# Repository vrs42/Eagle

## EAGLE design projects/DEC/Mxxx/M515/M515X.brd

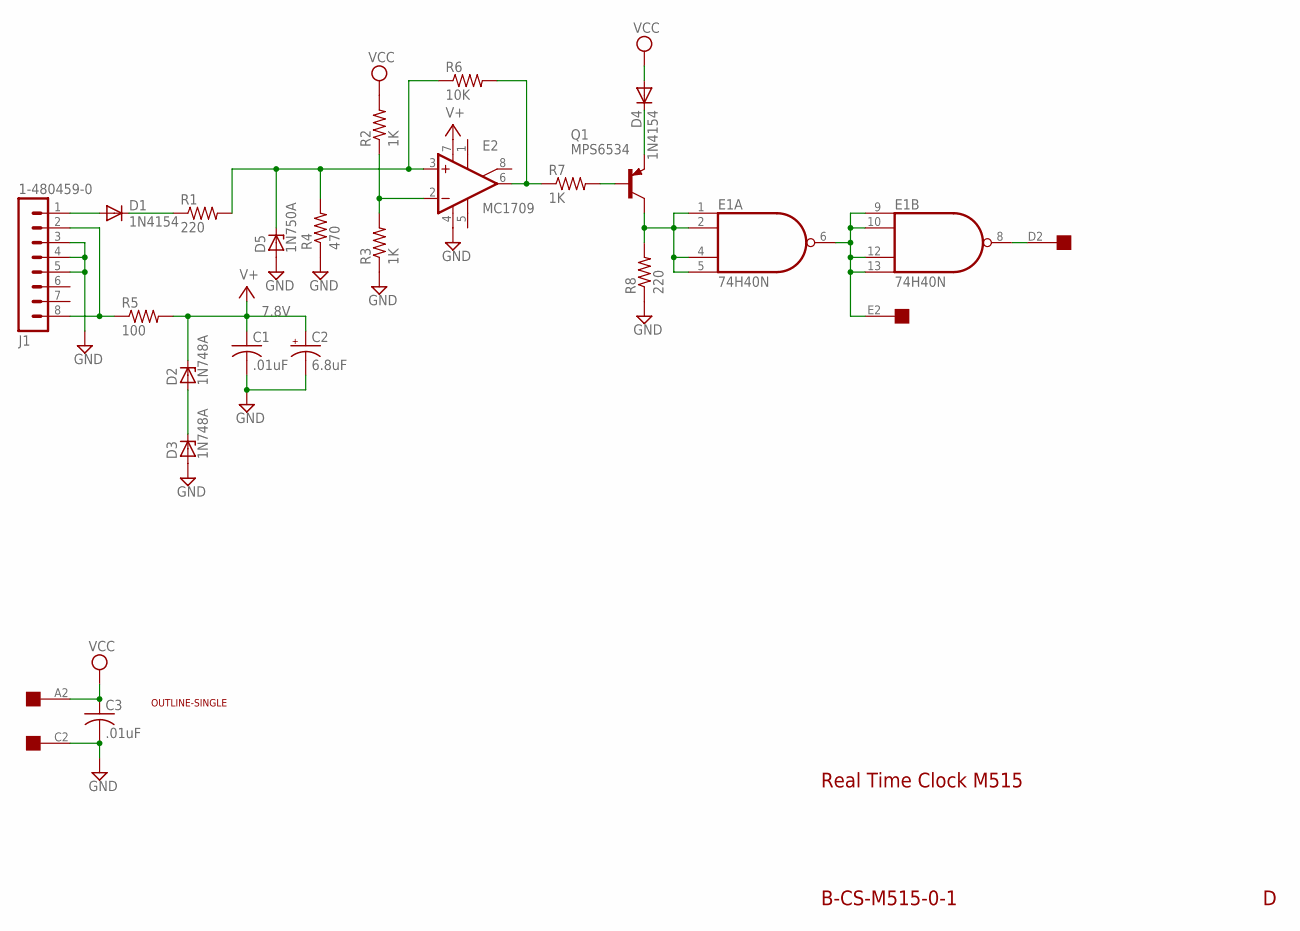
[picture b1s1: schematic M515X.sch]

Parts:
C1, C3: .01uF; C050-025X075
C2: 6.8uF; E12-8
D1, D4: 1N4154; DO35-10
D2, D3: 1N748A; DO35Z10
D5: 1N750A; DO35Z10
E1: 74H40N; DIL14
E2: MC1709; H08C
J1: 1-480459-0
Q1: MPS6534; TO5
R1, R8: 220; 0207/10
R2, R3, R7: 1K; 0207/10
R4: 470; 0207/10
R5: 100; 0207/10
R6: 10K; 0207/10
U$1: OUTLINE-SINGLE; SINGLE
U$3: EDGE-1; EDGE-CON1

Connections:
GND: C1.2, C2.-, C3.2, D3.A, D5.A, E1.7 (GND), E2.4 (V-), J1.3, J1.4, J1.5, R3.1, R4.1, R8.1, U$3.C2
unnamed: D1.A, J1.1
unnamed: D2.A, D3.C
unnamed: J1.2, J1.8, R5.1
unnamed: D1.C, R1.1
unnamed: D5.C, E2.3 (+IN), R1.2, R4.2, R6.1
unnamed: E1.8 (O), U$3.D2
unnamed: E1.6 (O), E1.9 (I0), E1.10 (I1), E1.12 (I2), E1.13 (I3), U$3.E2
unnamed: E1.1 (I0), E1.2 (I1), E1.4 (I2), E1.5 (I3), Q1.3 (C), R8.2
unnamed: D4.C, Q1.1 (E)
unnamed: Q1.2 (B), R7.2
unnamed: E2.6 (OUT), R6.2, R7.1
unnamed: E2.2 (-IN), R2.1, R3.2
V+: C1.1, C2.+, D2.C, E2.7 (V+), R5.2
VCC: C3.1, D4.A, E1.14 (VCC), R2.2, U$3.A2

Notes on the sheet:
7.8V
B-CS-M515-0-1
Real Time Clock M515

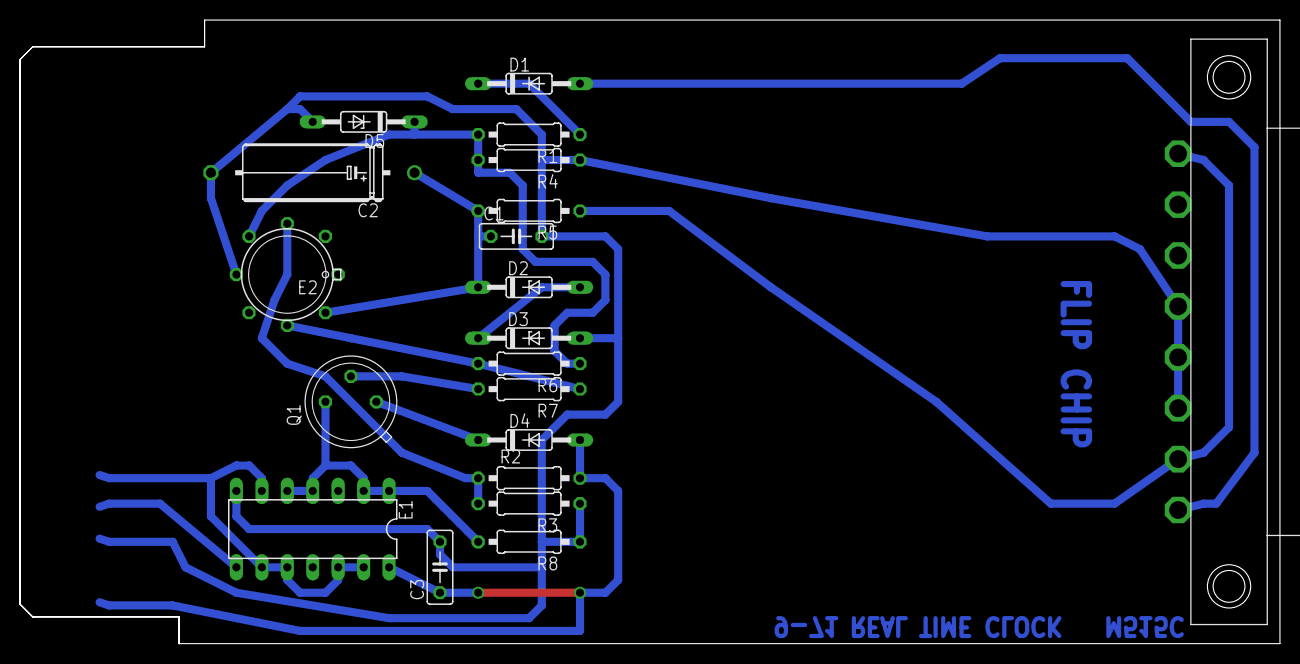
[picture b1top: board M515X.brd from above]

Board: 2 copper layers, 125.7 x 62.2 mm, 22 parts (0 on the bottom side), 15 nets.

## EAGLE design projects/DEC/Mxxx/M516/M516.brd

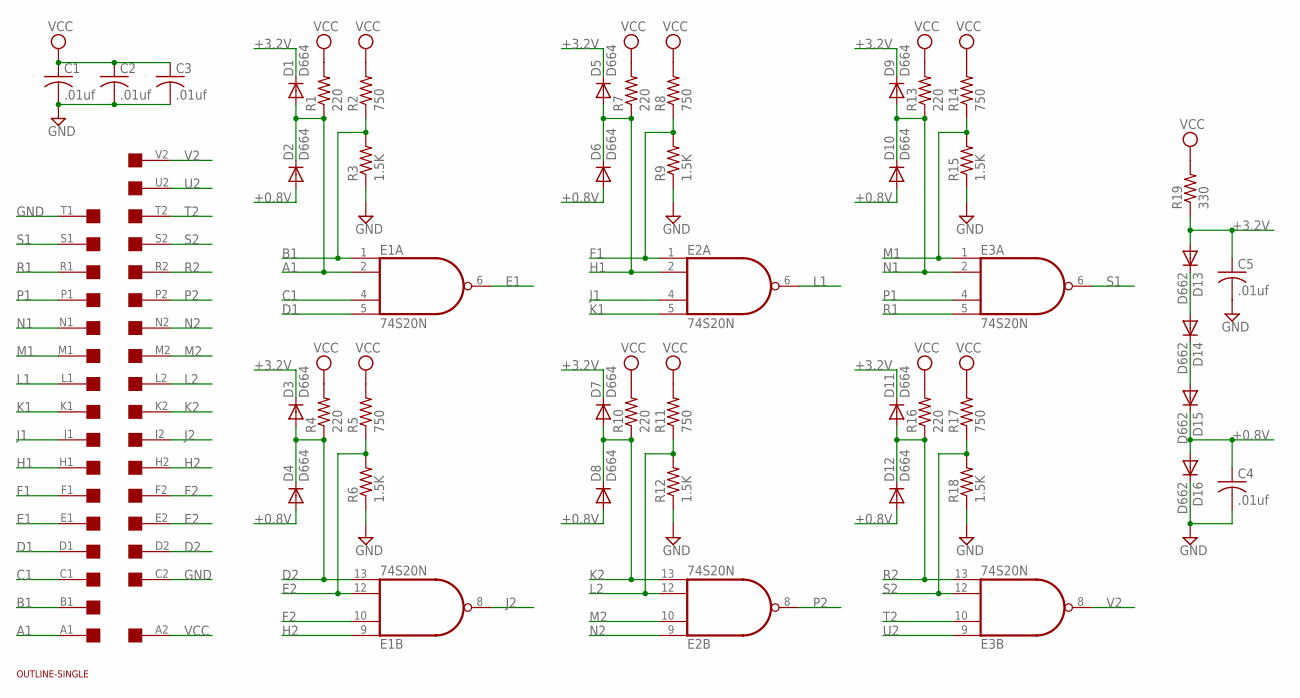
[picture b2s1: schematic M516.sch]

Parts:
C1, C2, C3, C4, C5: .01uf; C050-025X075
D1, D2, D3, D4, D5, D6, D7, D8, D9, D10, D11, D12: D664; DO35-10
D13, D14, D15, D16: D662; DO35-10
E1, E2, E3: 74S20N; DIL14
R1, R4, R7, R10, R13, R16: 220; 0207/10
R2, R5, R8, R11, R14, R17: 750; 0207/10
R3, R6, R9, R12, R15, R18: 1.5K; 0207/10
R19: 330; 0207/10
U$1: OUTLINE-SINGLE; SINGLE
U$2: SINGLE; EDGE-CON2

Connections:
+0.8V: C4.1, D2.A, D4.A, D6.A, D8.A, D10.A, D12.A, D15.C, D16.A
+3.2V: C5.1, D1.C, D3.C, D5.C, D7.C, D9.C, D11.C, D13.A, R19.1
A1: D1.A, D2.C, E1.2 (I1), R1.1, U$2.A1
B1: E1.1 (I0), R2.1, R3.2, U$2.B1
C1: E1.4 (I2), U$2.C1
D1: E1.5 (I3), U$2.D1
D2: D3.A, D4.C, E1.13 (I3), R4.1, U$2.D2
E1: E1.6 (O), U$2.E1
E2: E1.12 (I2), R5.1, R6.2, U$2.E2
F1: E2.1 (I0), R8.1, R9.2, U$2.F1
F2: E1.10 (I1), U$2.F2
GND: C1.2, C2.2, C3.2, C4.2, C5.2, D16.C, E1.7 (GND), E2.7 (GND), E3.7 (GND), R3.1, R6.1, R9.1, R12.1, R15.1, R18.1, U$2.C2, U$2.T1
H1: D5.A, D6.C, E2.2 (I1), R7.1, U$2.H1
H2: E1.9 (I0), U$2.H2
J1: E2.4 (I2), U$2.J1
J2: E1.8 (O), U$2.J2
K1: E2.5 (I3), U$2.K1
K2: D7.A, D8.C, E2.13 (I3), R10.1, U$2.K2
L1: E2.6 (O), U$2.L1
L2: E2.12 (I2), R11.1, R12.2, U$2.L2
M1: E3.1 (I0), R14.1, R15.2, U$2.M1
M2: E2.10 (I1), U$2.M2
N1: D9.A, D10.C, E3.2 (I1), R13.1, U$2.N1
N2: E2.9 (I0), U$2.N2
unnamed: D13.C, D14.A
unnamed: D14.C, D15.A
P1: E3.4 (I2), U$2.P1
P2: E2.8 (O), U$2.P2
R1: E3.5 (I3), U$2.R1
R2: D11.A, D12.C, E3.13 (I3), R16.1, U$2.R2
S1: E3.6 (O), U$2.S1
S2: E3.12 (I2), R17.1, R18.2, U$2.S2
T2: E3.10 (I1), U$2.T2
U2: E3.9 (I0), U$2.U2
V2: E3.8 (O), U$2.V2
VCC: C1.1, C2.1, C3.1, E1.14 (VCC), E2.14 (VCC), E3.14 (VCC), R1.2, R2.2, R4.2, R5.2, R7.2, R8.2, R10.2, R11.2, R13.2, R14.2, R16.2, R17.2, R19.2, U$2.A2

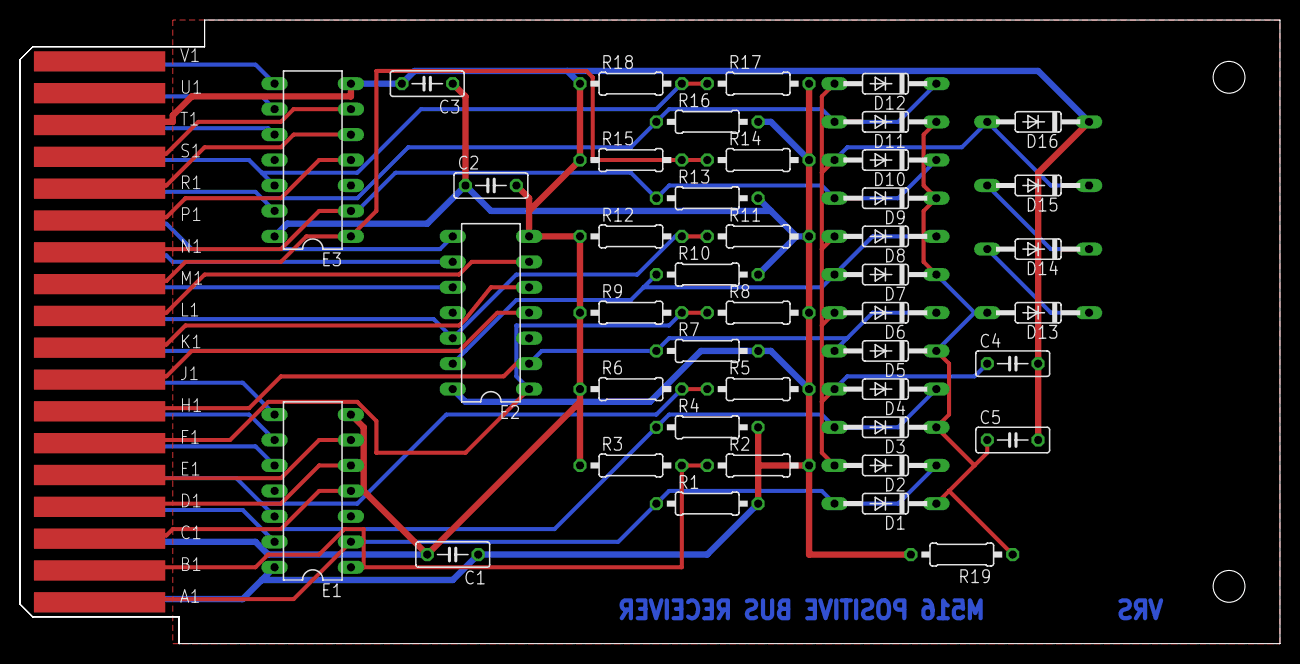
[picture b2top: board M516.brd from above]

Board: 2 copper layers, 125.7 x 62.2 mm, 45 parts (0 on the bottom side), 36 nets.

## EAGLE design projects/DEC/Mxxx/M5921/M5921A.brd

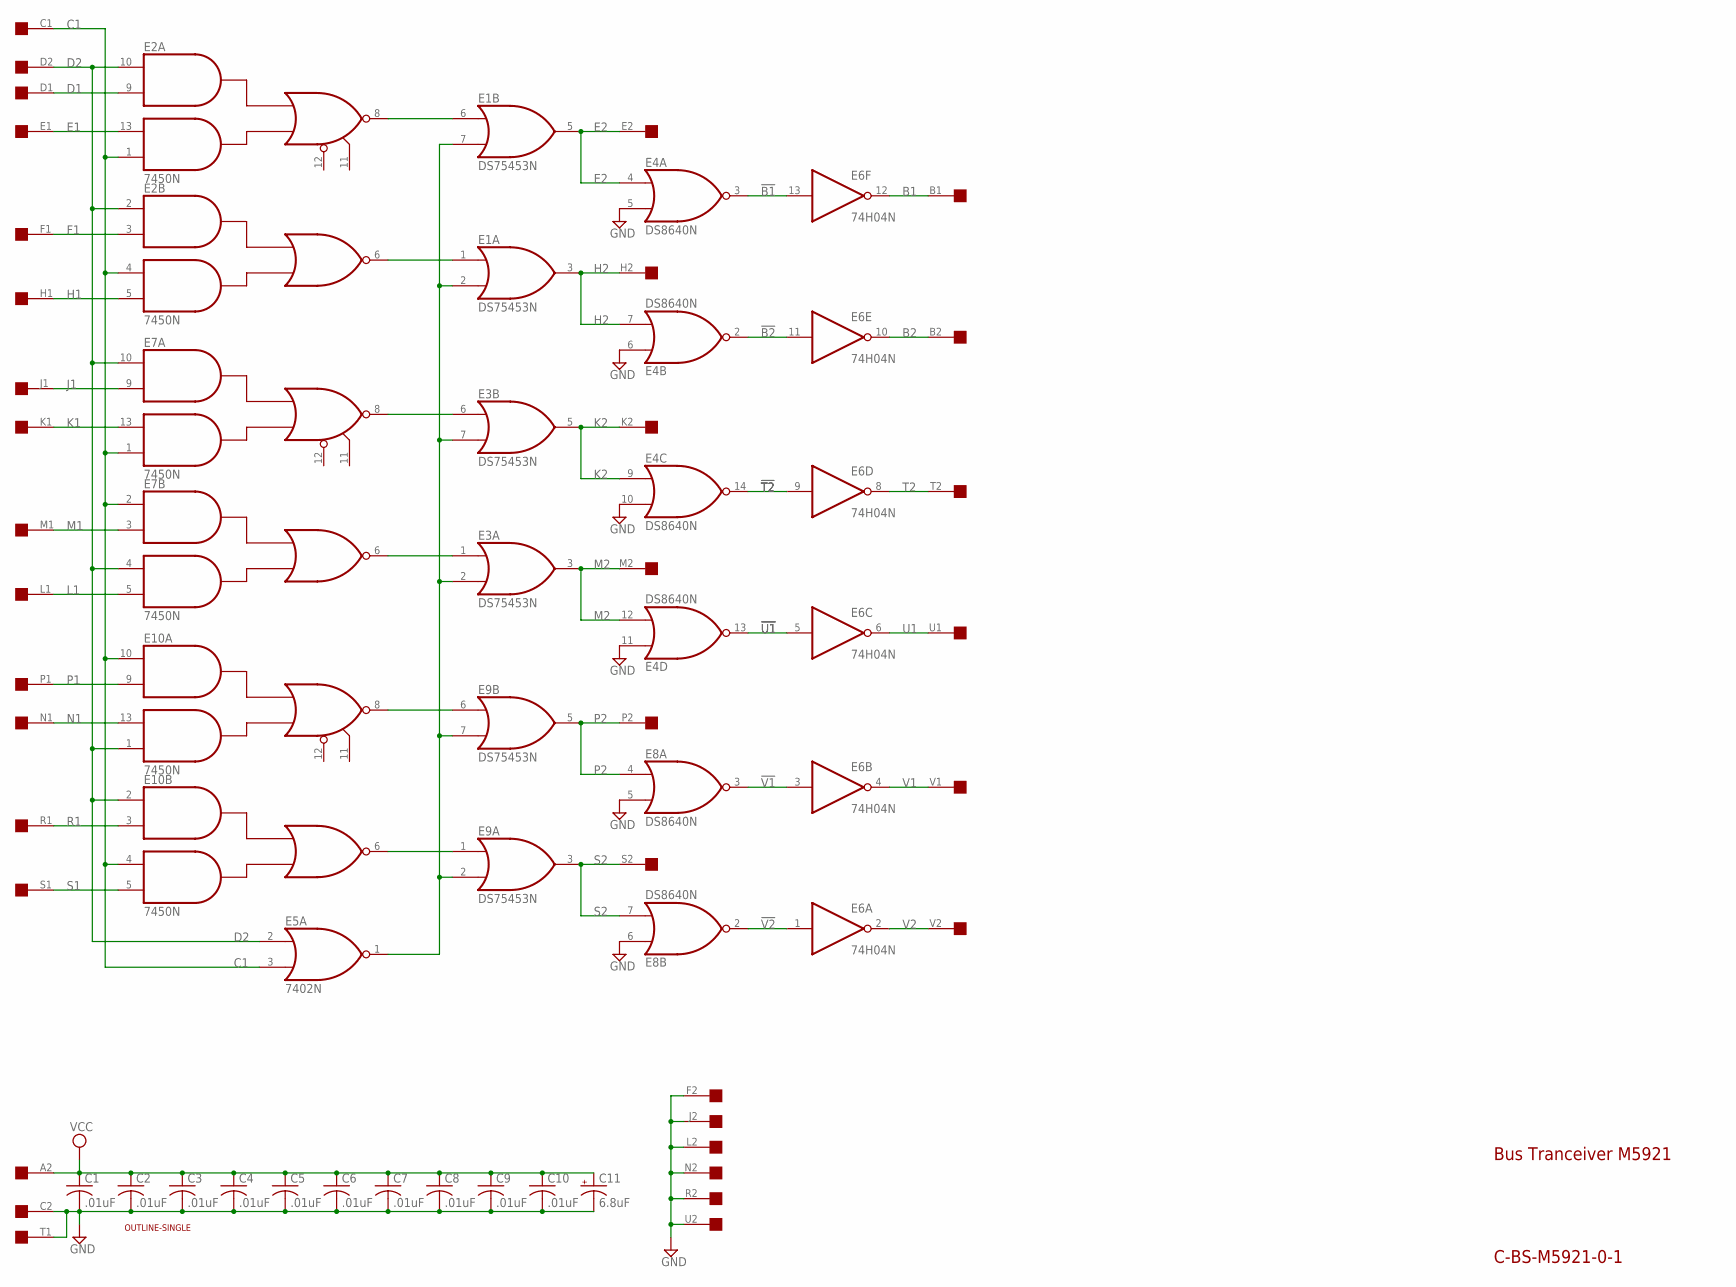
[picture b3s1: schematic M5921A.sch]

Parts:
C1, C2, C3, C4, C5, C6, C7, C8, C9, C10: .01uF; C063-025X075
C11: 6.8uF; E15-5
E1, E3, E9: DS75453N; DIL08
E2, E7, E10: 7450N; DIL14
E4, E8: DS8640N; DIL14
E5: 7402N; DIL14
E6: 74H04N; DIL14
U$1: OUTLINE-SINGLE; SINGLE
U$2: edge; EDGE-CON2

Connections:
!B1: E4.3 (O), E6.13 (I)
!B2: E4.2 (O), E6.11 (I)
!T2: E4.14 (O), E6.9 (I)
!U1: E4.13 (O), E6.5 (I)
!V1: E6.3 (I), E8.3 (O)
!V2: E6.1 (I), E8.2 (O)
B1: E6.12 (O), U$2.B1
B2: E6.10 (O), U$2.B2
C1: E2.1 (I4), E2.4 (I3), E5.3 (I1), E7.1 (I4), E7.2 (I1), E10.4 (I3), E10.10 (I1), U$2.C1
D1: E2.9 (I2), U$2.D1
D2: E2.2 (I1), E2.10 (I1), E5.2 (I0), E7.4 (I3), E7.10 (I1), E10.1 (I4), E10.2 (I1), U$2.D2
E1: E2.13 (I3), U$2.E1
E2: E1.5 (O), E4.4 (I0), U$2.E2
F1: E2.3 (I2), U$2.F1
GND: C1.2, C2.2, C3.2, C4.2, C5.2, C6.2, C7.2, C8.2, C9.2, C10.2, C11.-, E1.4 (GND), E2.7 (GND), E3.4 (GND), E4.1 (GND), E4.5 (I1), E4.6 (I0), E4.10 (I1), E4.11 (I0), E5.7 (GND), E6.7 (GND), E7.7 (GND), E8.1 (GND), E8.5 (I1), E8.6 (I0), E9.4 (GND), E10.7 (GND), U$2.C2, U$2.F2, U$2.J2, U$2.L2, U$2.N2, U$2.R2, U$2.T1, U$2.U2
H1: E2.5 (I4), U$2.H1
H2: E1.3 (O), E4.7 (I1), U$2.H2
J1: E7.9 (I2), U$2.J1
K1: E7.13 (I3), U$2.K1
K2: E3.5 (O), E4.9 (I0), U$2.K2
L1: E7.5 (I4), U$2.L1
M1: E7.3 (I2), U$2.M1
M2: E3.3 (O), E4.12 (I1), U$2.M2
N1: E10.13 (I3), U$2.N1
unnamed: E1.1 (I0), E2.6 (O)
unnamed: E1.6 (I0), E2.8 (O)
unnamed: E1.2 (I1), E1.7 (I1), E3.2 (I1), E3.7 (I1), E5.1 (O), E9.2 (I1), E9.7 (I1)
unnamed: E3.6 (I0), E7.8 (O)
unnamed: E3.1 (I0), E7.6 (O)
unnamed: E9.6 (I0), E10.8 (O)
unnamed: E9.1 (I0), E10.6 (O)
P1: E10.9 (I2), U$2.P1
P2: E8.4 (I0), E9.5 (O), U$2.P2
R1: E10.3 (I2), U$2.R1
S1: E10.5 (I4), U$2.S1
S2: E8.7 (I1), E9.3 (O), U$2.S2
T2: E6.8 (O), U$2.T2
U1: E6.6 (O), U$2.U1
V1: E6.4 (O), U$2.V1
V2: E6.2 (O), U$2.V2
VCC: C1.1, C2.1, C3.1, C4.1, C5.1, C6.1, C7.1, C8.1, C9.1, C10.1, C11.+, E1.8 (VCC), E2.14 (VCC), E3.8 (VCC), E4.8 (VCC), E5.14 (VCC), E6.14 (VCC), E7.14 (VCC), E8.8 (VCC), E9.8 (VCC), E10.14 (VCC), U$2.A2

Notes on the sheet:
Bus Tranceiver M5921
C-BS-M5921-0-1

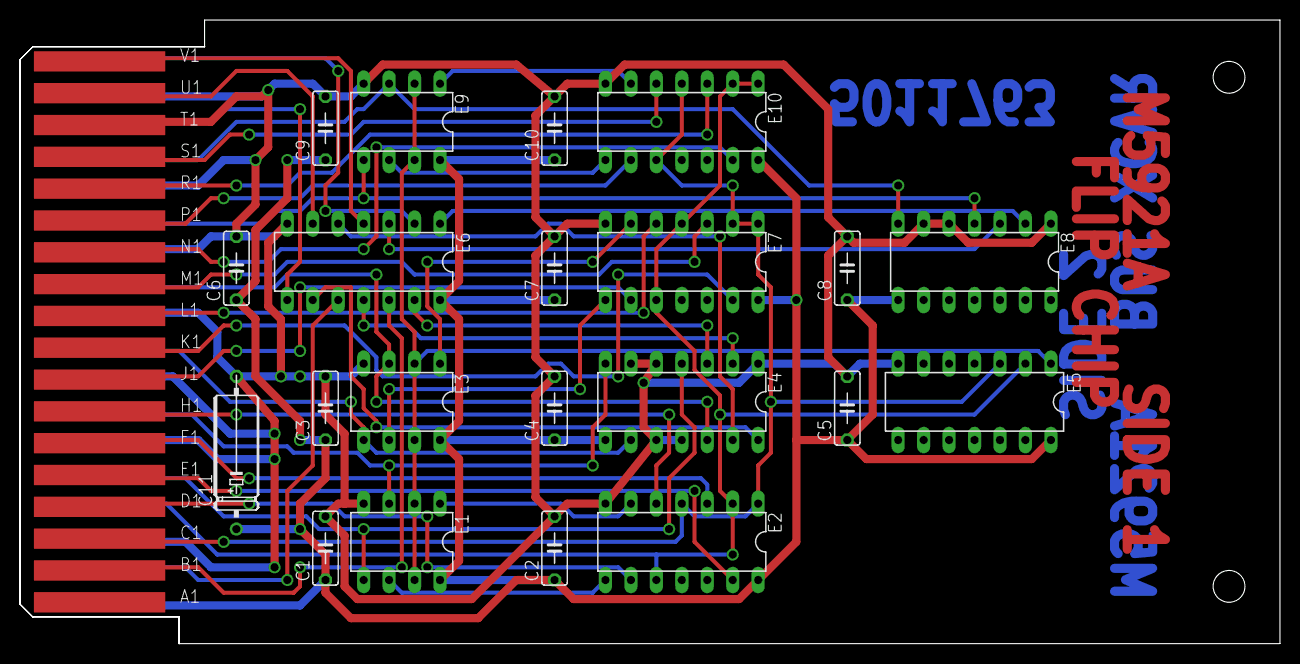
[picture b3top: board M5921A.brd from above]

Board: 2 copper layers, 125.7 x 62.2 mm, 23 parts (0 on the bottom side), 41 nets.

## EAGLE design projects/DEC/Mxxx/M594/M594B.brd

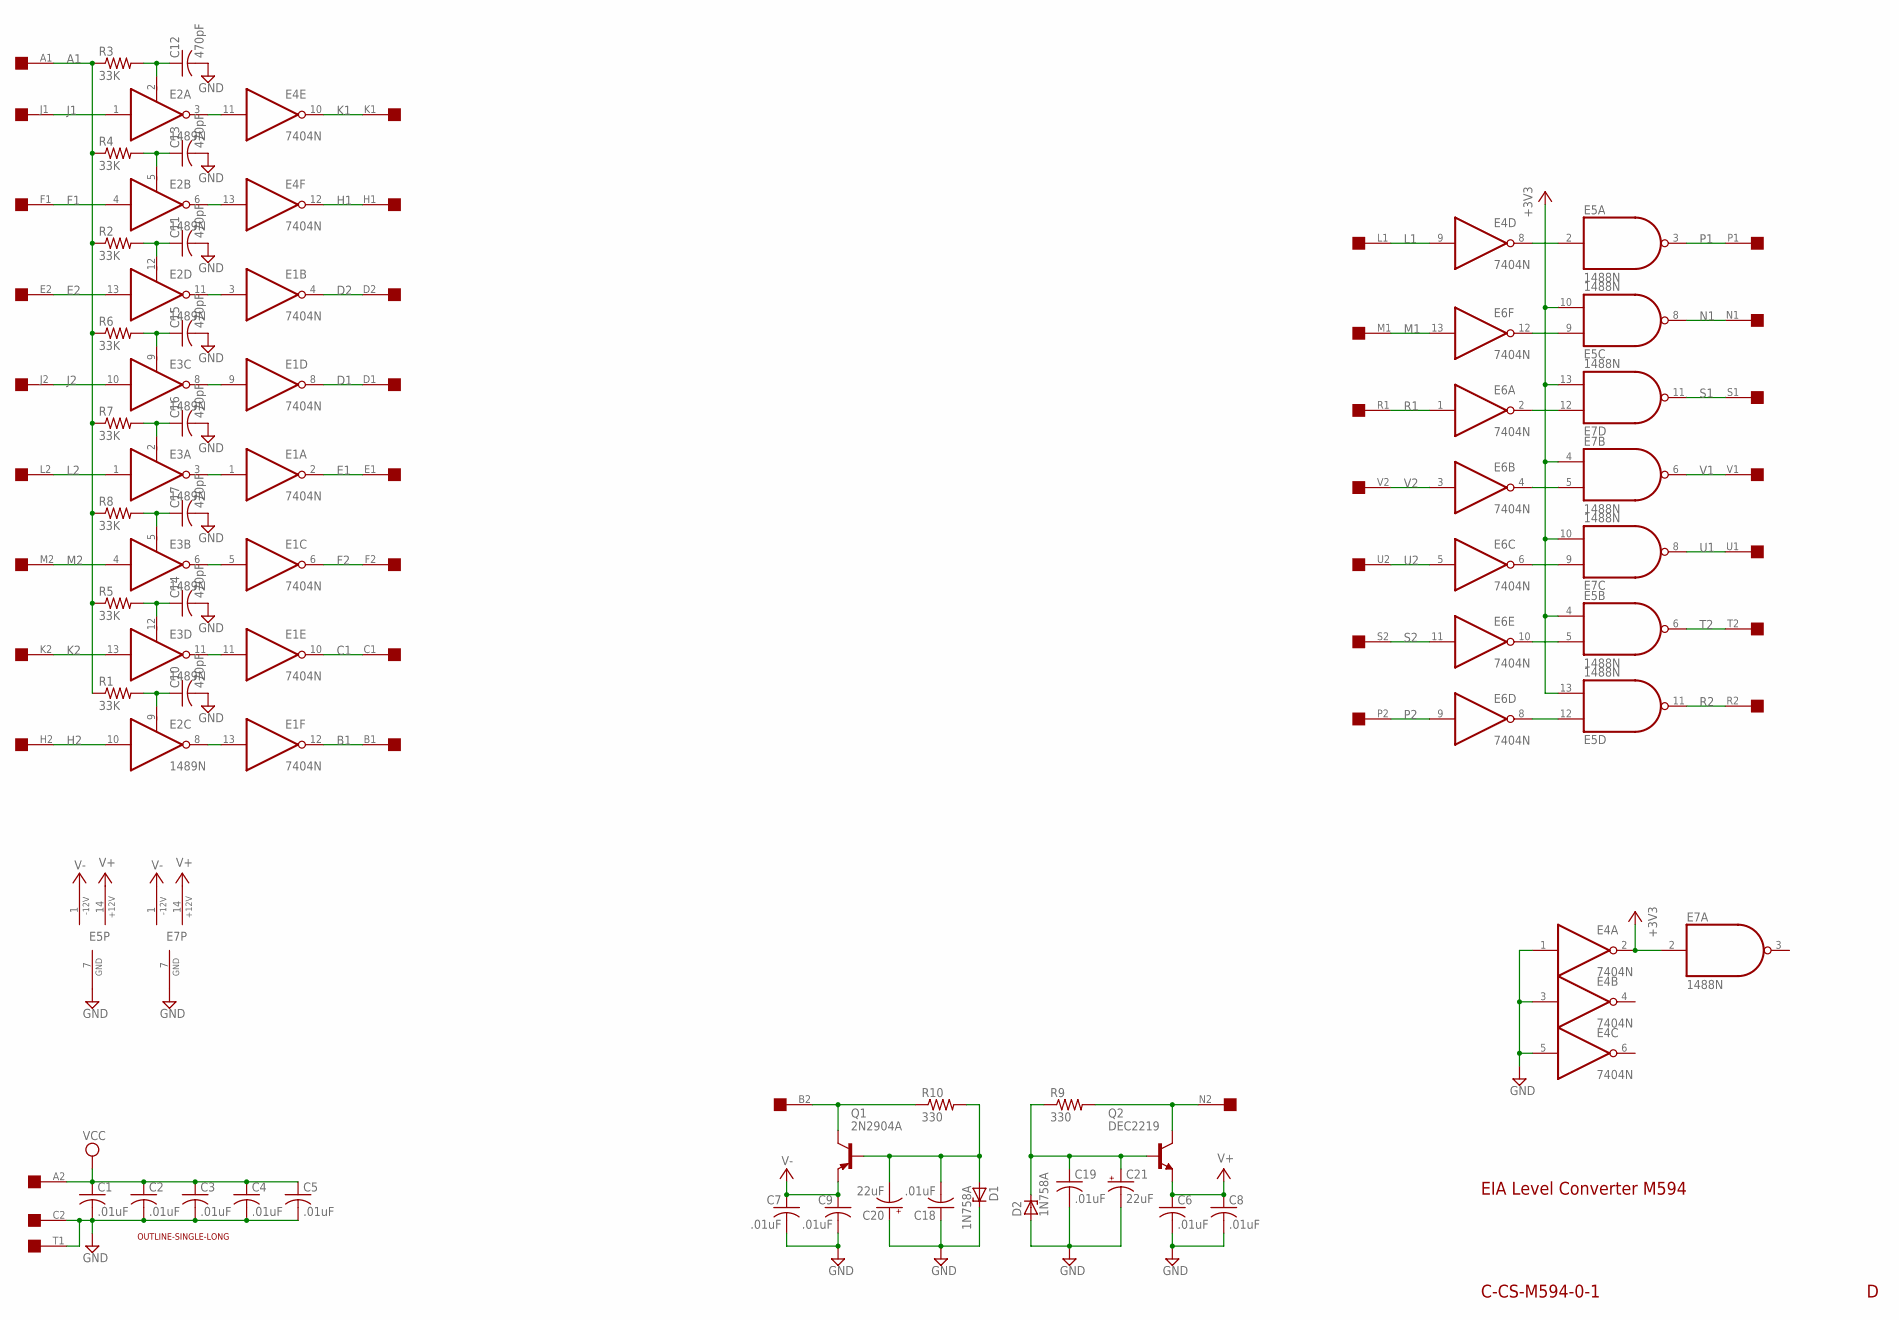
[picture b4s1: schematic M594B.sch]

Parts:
C1, C2, C3, C4, C5, C6, C7, C8, C9, C18, C19: .01uF; C050-025X075
C10, C11, C12, C13, C14, C15, C16, C17: 470pF; C075-032X103
C20, C21: 22uF; E12-8
D1, D2: 1N758A; DO35Z10
E1, E4, E6: 7404N; DIL14
E2, E3: 1489N; DIL14
E5, E7: 1488N; DIL14
Q1: 2N2904A; TO5
Q2: DEC2219; TO5
R1, R2, R3, R4, R5, R6, R7, R8: 33K; 0207/10
R9, R10: 330; 0207/10
U$1: OUTLINE-SINGLE-LONG; SINGLE-LONG
U$2: SINGLE; EDGE-CON2

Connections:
+3V3: E4.2 (O), E5.4 (I0), E5.10 (I1), E5.13 (I1), E7.2 (I), E7.4 (I0), E7.10 (I1), E7.13 (I1)
A1: R1.1, R2.1, R3.1, R4.1, R5.1, R6.1, R7.1, R8.1, U$2.A1
B1: E1.12 (O), U$2.B1
B2: Q1.3 (C), R10.1, U$2.B2
C1: E1.10 (O), U$2.C1
D1: E1.8 (O), U$2.D1
D2: E1.4 (O), U$2.D2
E1: E1.2 (O), U$2.E1
E2: E2.13 (I), U$2.E2
F1: E2.4 (I), U$2.F1
F2: E1.6 (O), U$2.F2
GND: C1.2, C2.2, C3.2, C4.2, C5.2, C6.2, C7.2, C8.2, C9.2, C10.2, C11.2, C12.2, C13.2, C14.2, C15.2, C16.2, C17.2, C18.1, C19.2, C20.+, C21.-, D1.C, D2.A, E1.7 (GND), E2.7 (GND), E3.7 (GND), E4.1 (I), E4.3 (I), E4.5 (I), E4.7 (GND), E5.7 (GND), E6.7 (GND), E7.7 (GND), U$2.C2, U$2.T1
H1: E4.12 (O), U$2.H1
H2: E2.10 (I), U$2.H2
J1: E2.1 (I), U$2.J1
J2: E3.10 (I), U$2.J2
K1: E4.10 (O), U$2.K1
K2: E3.13 (I), U$2.K2
L1: E4.9 (I), U$2.L1
L2: E3.1 (I), U$2.L2
M1: E6.13 (I), U$2.M1
M2: E3.4 (I), U$2.M2
N1: E5.8 (O), U$2.N1
N2: Q2.3 (C), R9.2, U$2.N2
unnamed: C18.2, C20.-, D1.A, Q1.2 (B), R10.2
unnamed: C19.1, C21.+, D2.C, Q2.2 (B), R9.1
unnamed: E4.8 (O), E5.2 (I)
unnamed: E2.3 (O), E4.11 (I)
unnamed: E5.9 (I0), E6.12 (O)
unnamed: E6.2 (O), E7.12 (I0)
unnamed: E6.4 (O), E7.5 (I1)
unnamed: E6.6 (O), E7.9 (I0)
unnamed: E5.5 (I1), E6.10 (O)
unnamed: E5.12 (I0), E6.8 (O)
unnamed: E2.6 (O), E4.13 (I)
unnamed: E1.3 (I), E2.11 (O)
unnamed: E1.9 (I), E3.8 (O)
unnamed: E1.1 (I), E3.3 (O)
unnamed: E1.5 (I), E3.6 (O)
unnamed: E1.11 (I), E3.11 (O)
unnamed: E1.13 (I), E2.8 (O)
unnamed: C12.1, E2.2 (RC), R3.2
unnamed: C13.1, E2.5 (RC), R4.2
unnamed: C10.1, E2.9 (RC), R1.2
unnamed: C14.1, E3.12 (RC), R5.2
unnamed: C17.1, E3.5 (RC), R8.2
unnamed: C15.1, E3.9 (RC), R6.2
unnamed: C16.1, E3.2 (RC), R7.2
unnamed: C11.1, E2.12 (RC), R2.2
P1: E5.3 (O), U$2.P1
P2: E6.9 (I), U$2.P2
R1: E6.1 (I), U$2.R1
R2: E5.11 (O), U$2.R2
S1: E7.11 (O), U$2.S1
S2: E6.11 (I), U$2.S2
T2: E5.6 (O), U$2.T2
U1: E7.8 (O), U$2.U1
U2: E6.5 (I), U$2.U2
V1: E7.6 (O), U$2.V1
V2: E6.3 (I), U$2.V2
V+: C6.1, C8.1, E5.14 (+12V), E7.14 (+12V), Q2.1 (E)
V-: C7.1, C9.1, E5.1 (-12V), E7.1 (-12V), Q1.1 (E)
VCC: C1.1, C2.1, C3.1, C4.1, C5.1, E1.14 (VCC), E2.14 (VCC), E3.14 (VCC), E4.14 (VCC), E6.14 (VCC), U$2.A2

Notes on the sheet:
EIA Level Converter M594
C-CS-M594-0-1

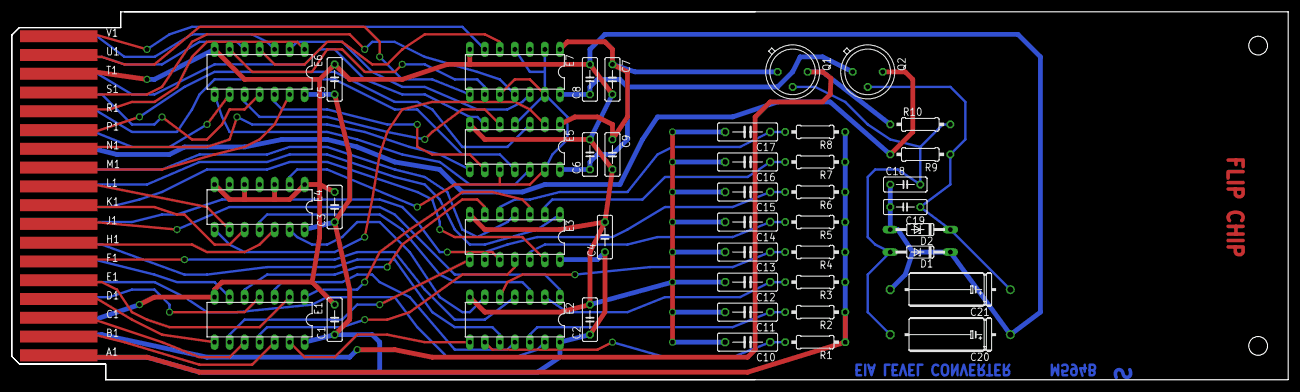
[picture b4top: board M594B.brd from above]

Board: 2 copper layers, 215.9 x 62.2 mm, 44 parts (0 on the bottom side), 63 nets.

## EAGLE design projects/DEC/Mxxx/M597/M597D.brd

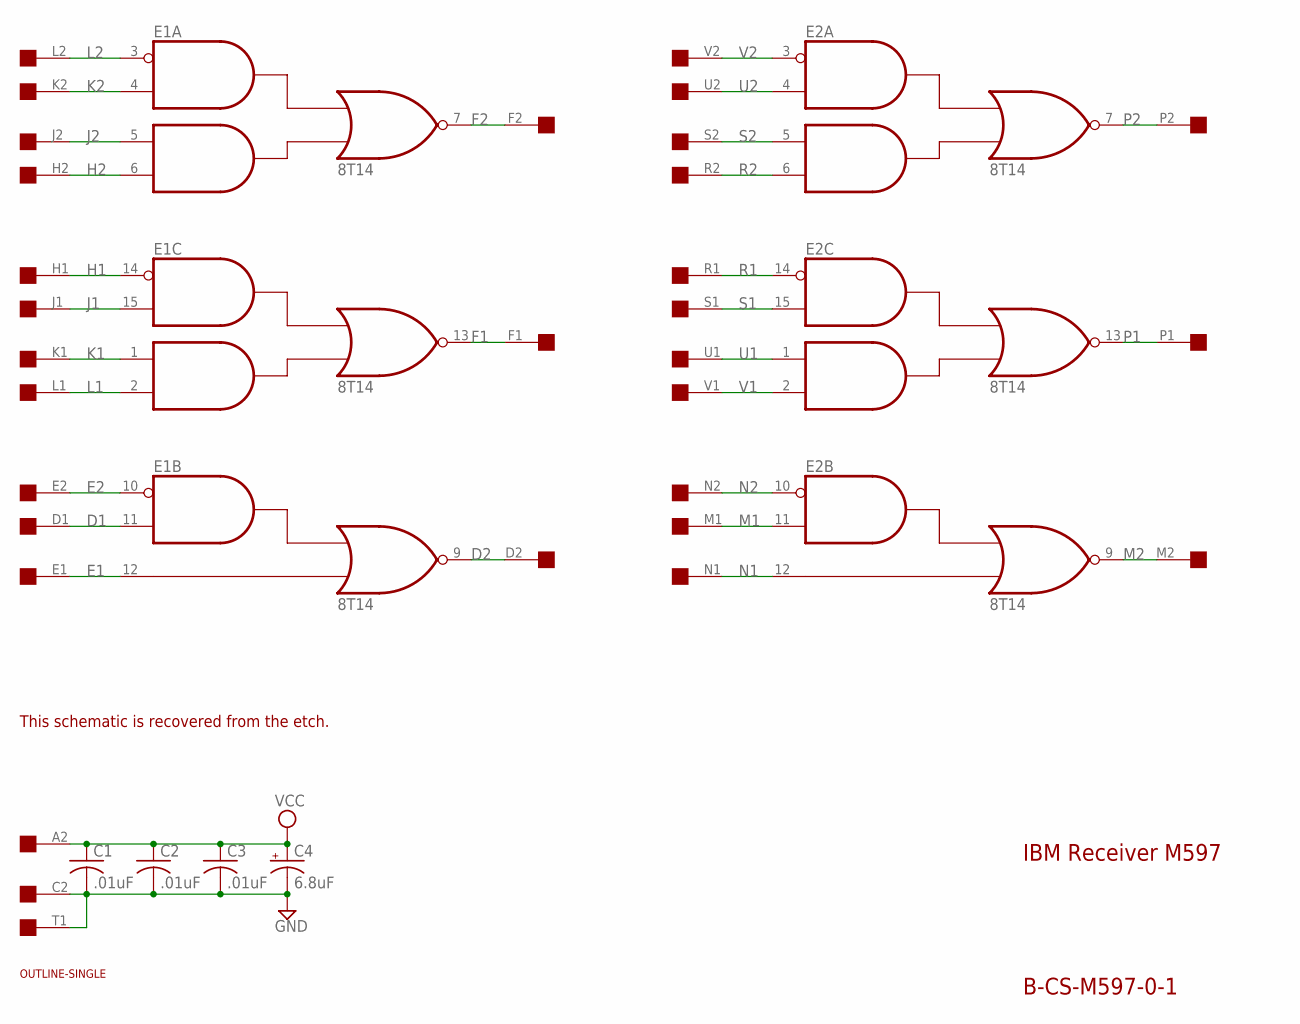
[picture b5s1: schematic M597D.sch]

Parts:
C1, C2, C3: .01uF; C050-025X075
C4: 6.8uF; E12-8
E1, E2: 8T14; DIL16
U$2: SINGLE; EDGE-CON2
U$4: OUTLINE-SINGLE; SINGLE

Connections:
D1: E1.11 (S), U$2.D1
D2: E1.9 (O), U$2.D2
E1: E1.12 (I1), U$2.E1
E2: E1.10 (R), U$2.E2
F1: E1.13 (O), U$2.F1
F2: E1.7 (O), U$2.F2
GND: C1.2, C2.2, C3.2, C4.-, E1.8 (GND), E2.8 (GND), U$2.C2, U$2.T1
H1: E1.14 (R), U$2.H1
H2: E1.6 (I2), U$2.H2
J1: E1.15 (S), U$2.J1
J2: E1.5 (I1), U$2.J2
K1: E1.1 (I1), U$2.K1
K2: E1.4 (S), U$2.K2
L1: E1.2 (I2), U$2.L1
L2: E1.3 (R), U$2.L2
M1: E2.11 (S), U$2.M1
M2: E2.9 (O), U$2.M2
N1: E2.12 (I1), U$2.N1
N2: E2.10 (R), U$2.N2
P1: E2.13 (O), U$2.P1
P2: E2.7 (O), U$2.P2
R1: E2.14 (R), U$2.R1
R2: E2.6 (I2), U$2.R2
S1: E2.15 (S), U$2.S1
S2: E2.5 (I1), U$2.S2
U1: E2.1 (I1), U$2.U1
U2: E2.4 (S), U$2.U2
V1: E2.2 (I2), U$2.V1
V2: E2.3 (R), U$2.V2
VCC: C1.1, C2.1, C3.1, C4.+, E1.16 (VCC), E2.16 (VCC), U$2.A2

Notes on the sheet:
IBM Receiver M597
B-CS-M597-0-1
This schematic is recovered from the etch.

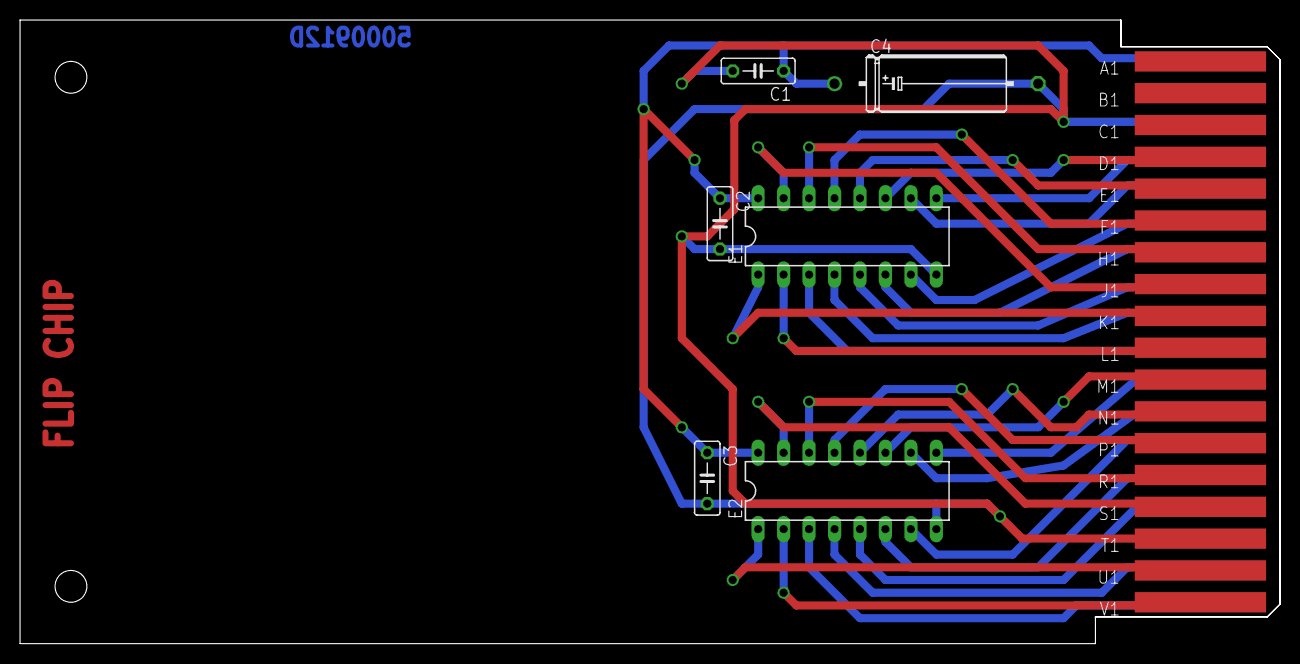
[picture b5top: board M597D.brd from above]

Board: 2 copper layers, 125.7 x 62.2 mm, 9 parts (0 on the bottom side), 30 nets.

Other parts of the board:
U$1: FLIPCHIP
